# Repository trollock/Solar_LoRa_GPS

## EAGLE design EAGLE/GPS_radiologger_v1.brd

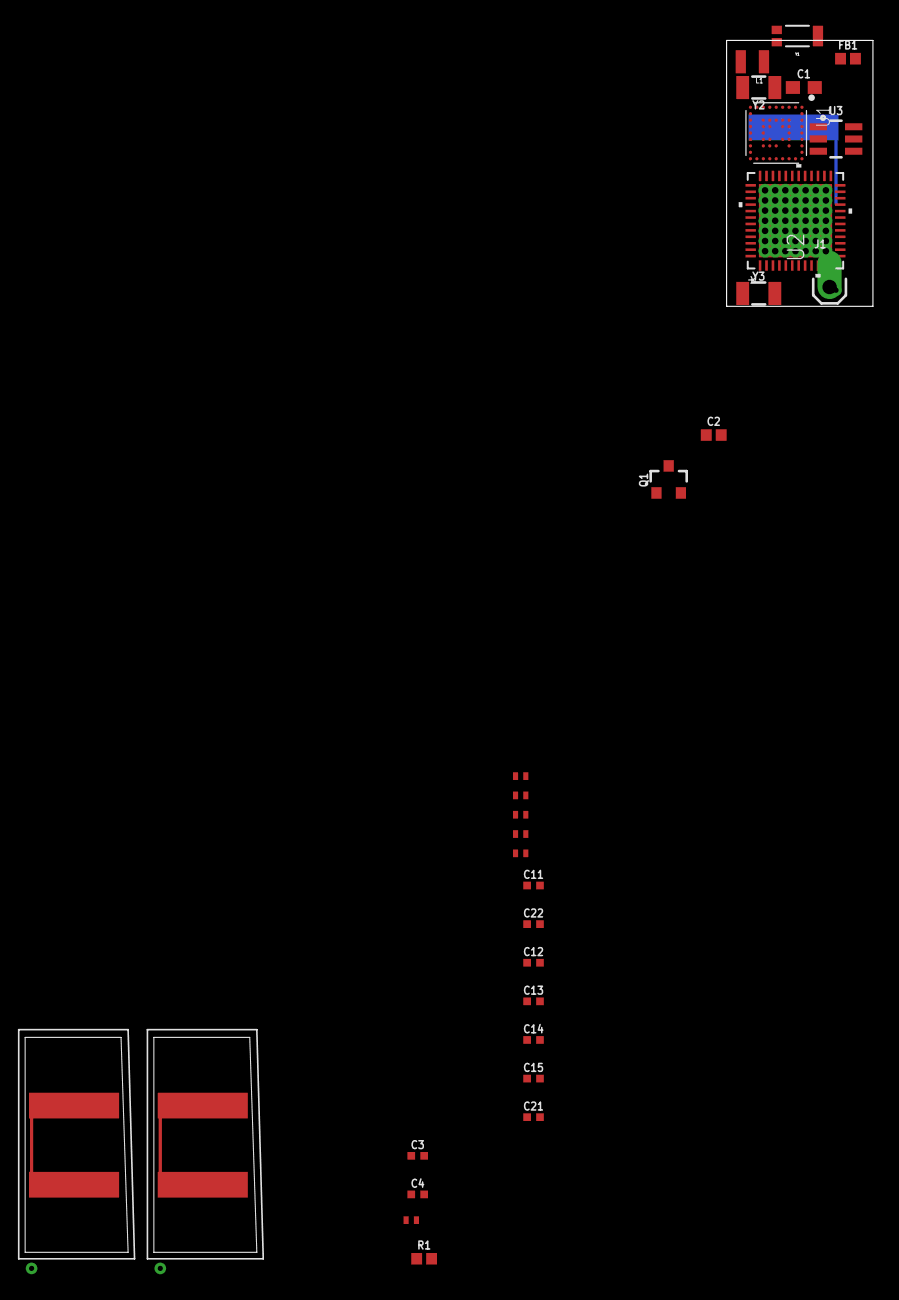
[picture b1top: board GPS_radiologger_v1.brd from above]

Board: 2 copper layers, 11.4 x 20.7 mm, 31 parts (1 on the bottom side), 21 nets, no tracks yet.

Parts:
C1: 4.7pF; 0603
C2: 0.1uF; 0402
C3, C4, C13: 12 pF; 0402-TIGHT
C11, C22: 8.2 pF; 0402-TIGHT
C12, C14: 4.7 pF; 0402-TIGHT
C15, C21: 330 pF; 0402-TIGHT
FB1: 120 Ohm; 0402
J1: 1X01_OFFSET
L1: 2.2 uH; 0806
L11: 33 nH; 0402_MURATA
L12, L21: 15 nH; 0402_MURATA
L13, L14: 20 nH; 0402_MURATA
Q1: 1.1A/60V/600mΩ; SOT23-3
R1: 100K; 0402
U1: UBLOX_ZOE_M8Q-0-10; UBLOX_ZOE_M8-0-10
U2: CC1350F128RGZT; RGZ48
U3: TPL5110; SOT23-6
U$1, U$2, U$4: TRISOLX_8X16
U$3: 2.4 pF; 0402_MURATA
Y1: GPS_CHIP_ANTENNAW3011; W3011
Y2, Y3: 32.768kHz; CRYSTAL-SMD-3.2X1.5MM

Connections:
3.3V: C2.1, U1.24, U1.25
DONE: U2.11, U3.4
DRIVE: Q1.1, U3.5
GND: C1.2, C2.2, C3.2, C4.2, C11.2, C12.2, C13.2, C14.2, C21.2, U1.1, U1.3, U1.5, U1.7, U1.8, U1.9, U1.10, U1.11, U1.12, U1.17, U1.23, U1.29, U1.31, U1.37, U1.38, U1.39, U1.40, U1.41, U1.44, U1.46, U1.47, U1.49, U3.2, U$3.P$2
unnamed: C1.1, L1.1, U1.27
unnamed: L1.2, U1.26
unnamed: U1.18, Y2.P$2
unnamed: U1.19, Y2.P$1
unnamed: U3.1, U3.6
unnamed: C13.1, L13.P$2, L14.P$1
unnamed: C14.1, C15.1, L14.P$2
unnamed: C12.1, C22.1, L12.P$2, L13.P$1
unnamed: C15.2, J1.1
unnamed: C3.1, U2.4, Y3.P$1
unnamed: C4.1, U2.5, Y3.P$2
unnamed: R1.1, U2.35, U$3.P$1
RF_N: C22.2, L11.P$2, L21.P$2, U2.2
RF_P: C11.1, L11.P$1, L12.P$1, U2.1
RX_TX: C21.1, L21.P$1, U2.3
SCL: U1.32, U2.9
SDA: U1.2, U2.10

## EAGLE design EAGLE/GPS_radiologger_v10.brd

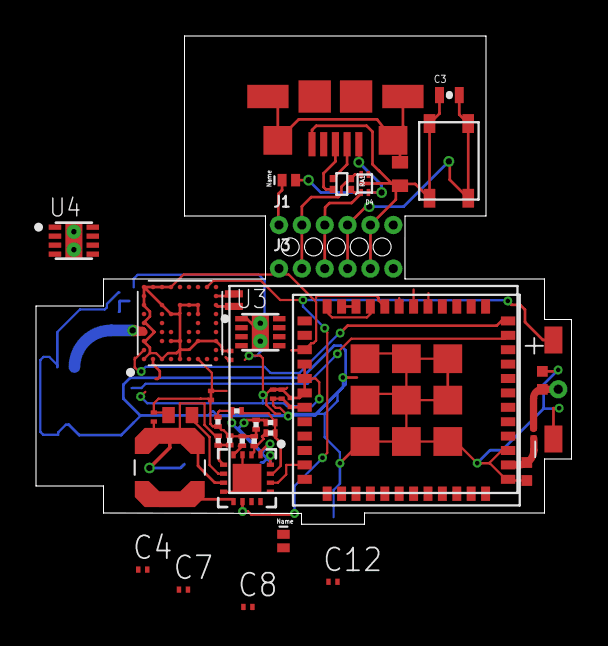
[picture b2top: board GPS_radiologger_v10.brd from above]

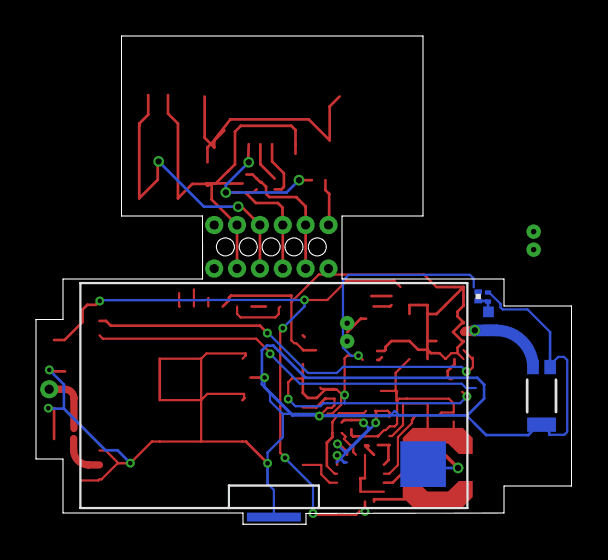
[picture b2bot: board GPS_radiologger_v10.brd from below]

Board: 2 copper layers, 29.8 x 27.1 mm, 47 parts (5 on the bottom side), 40 nets.

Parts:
C1: 47 pF; C0201
C2, C7, C12: 10 uF; C0201
C3: 100 nF; 0402-CAP
C4, C5, C8: 4.7 uF; C0201
C6, C10, C11: 0.1 uF; C0201
C9: 1 uF; C0201
C14: 4.7uF; C0201
C15: 10uF; C0402
D1, D2: CDSQR4148-HF
D4: USBULC6-2N4
FB1: FERRITE_BEAD-120_OHM_TIGHT; 0402-TIGHT
J1, J3: 1X06_1.27MM
J2: 1X01_SMALL
J4: 1981584-1
L1: BLM15HB121SN1; 0402
L3, L4: FERRITE_BEAD-120_OHM_TIGHT; 0402-TIGHT
L5: 22 uH; IND_LPS4012-103MRB
R1: 10; R0201
R2: 6.34M; R0201
R3: 14.7M; R0201
R4: 20k; R0201
RA1: EXB24V
RPG1: 6.8M; R0201
RPG2: 3.3M; R0201
RSD1: 6.49M; R0201
RSD2: 3.48M; R0201
RTERM1: 4.32M; R0201
RTERM2: 5.62M; R0201
U1: TYPEABZ
U2: UBLOX_ZOE_M8-0-10
U3, U4: MICROCHIP_MCP1810T-33I-J8AMICROCHIP_MCP1810T-33I-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; MICROCHIP_MCP1810T-33I-J8A_0
U$1: GMB301016
U$3: ADP5090; LFCSP-16-3X3
U$4: ICARUS_FULL
U$6: C&KTACTILESWITCH
Y1: 32.768kHz; CRYSTAL-SMD-1.0X1.2MM
Y2: W3011

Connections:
ANT: C11.1, J2.P$1, L4.1
BAT: U2.16, U$1.+, U$3.10
BOOT: J3.6, U1.P$43
DCDC_OUT: D2.P$2, U$3.11
DIS_SW: U1.P$11, U$3.14
DM: J3.2, U1.P$2
DM1: D4.P$4, J1.2, RA1.P$1
DP: J3.3, U1.P$1
DP1: D4.P$1, J1.3, RA1.P$2
GND: C1.2, C2.1, C3.1, C4.2, C5.2, C6.2, C7.2, C8.2, C9.1, C10.1, C12.2, C14.2, C15.2, D4.P$5, J1.5, J3.5, J4.5, L1.2, L3.2, L4.2, R3.1, R4.1, RPG2.1, RSD2.1, RTERM2.1, U1.P$3, U1.P$7, U1.P$25, U1.P$27, U1.P$44, U1.P$49, U1.P$50, U1.P$51, U1.P$52, U1.P$53, U1.P$54, U1.P$55, U1.P$56, U1.P$57, U2.1, U2.3, U2.5, U2.7, U2.8, U2.9, U2.10, U2.11, U2.12, U2.17, U2.23, U2.29, U2.31, U2.37, U2.38, U2.39, U2.40, U2.41, U2.44, U2.46, U2.47, U2.49, U3.1, U3.9, U4.1, U4.9, U$1.-, U$4.P$2, U$6.P$3, U$6.P$4, Y2.2, Y2.3
GPS_ANT: FB1.1, U2.4, Y2.1
GPS_PWR: C5.1, C6.1, C7.1, R1.2, U2.24, U2.25, U2.27, U4.2, U4.6
MCU_PWR: C2.2, C9.2, C10.2, C12.1, U1.P$4, U1.P$5, U1.P$6, U3.2, U3.6
unnamed: U1.P$45, U1.P$48
unnamed: D1.P$1, J1.1
unnamed: L5.2, U$3.9
unnamed: U$3.3, U$3.8, U$3.EXP
unnamed: R2.1, R3.2, U$3.5
unnamed: C15.1, U$3.6
unnamed: C1.1, FB1.2, R1.1
unnamed: R4.2, U$3.4
unnamed: RTERM1.1, RTERM2.2, U$3.2
unnamed: RPG1.1, RPG2.2, U$3.16
unnamed: U2.18, Y1.P$2
unnamed: U2.19, Y1.P$1
unnamed: RSD1.1, RSD2.2, U$3.1
unnamed: RPG1.2, RSD1.2, RTERM1.2, U$3.15
unnamed: C4.1, U4.7
unnamed: J4.3, RA1.P$4
unnamed: C11.2, L3.1, U1.P$26
unnamed: J4.2, RA1.P$3
RESET: C3.2, J1.4, U$6.P$1, U$6.P$2
RST: J3.4, U1.P$34
SCL: U1.P$35, U2.32
SDA: U1.P$36, U2.2
TCXO_OUT: U1.P$46, U1.P$47
USB_SHIELD: J4.S1, J4.S2, J4.S3, J4.S4, L1.1
VBUS: C8.1, D2.P$1, J3.1, U1.P$20, U3.7, U3.8
VBUS1: D1.P$2, D4.P$2, J4.1
VIN: C14.1, L5.1, R2.2, U$3.7, U$4.P$1

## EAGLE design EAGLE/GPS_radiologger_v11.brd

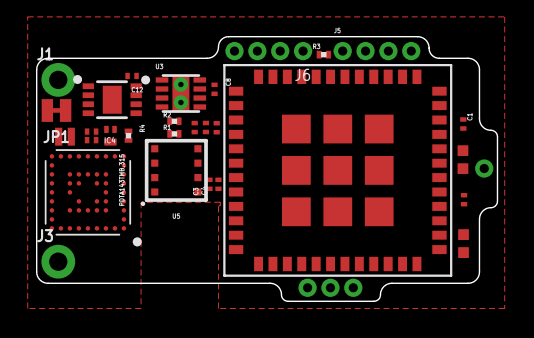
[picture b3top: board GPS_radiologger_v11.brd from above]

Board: 4 copper layers, 25.6 x 14.7 mm, 32 parts (1 on the bottom side), 24 nets, no tracks yet.

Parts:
C1, C3, C4, C6, C10, C11: 0.1 uF; C0201
C2, C12: 10 uF; C0201
C5, C8: 4.7 uF; C0201
C9: 1 uF; C0201
IC4: CAT24M01HU5I-GT3; SON50P300X200X55-9N
J1, J3: 1X01_NO_SILK
J2: 1X01_SMALL
J4: 1X03_1.27MM_NO_SILK
J5, J6: 1X04_1.27MM_NO_SILK
JP1: JUMPER-SMT_2_NC_TRACE_NO-SILK; SMT-JUMPER_2_NC_TRACE_NO-SILK
L3, L4: FERRITE_BEAD-120_OHM_TIGHT; 0402-TIGHT
PDTA143TMB,315: TINYPICO-PNPAMB; SOT883(B)
R1, R2: 4.7; R0201
R3: 10k; R0201
R4: 100k; R0201
U1: TYPEABZ
U2: UBLOX_ZOE_M8-0-10
U3: MICROCHIP_MCP1810T-33I-J8AMICROCHIP_MCP1810T-33I-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; MICROCHIP_MCP1810T-33I-J8A_0
U5: BME680BME680; LGA3.0X3.0
Y1: 32.768kHz; CRYSTAL-SMD-1.0X1.2MM
Y2: W3011

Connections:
ANT: C11.1, J2.P$1, L4.1
BAT: C8.1, J1.1, U1.P$32, U3.7, U3.8
BOOT: J5.1, R3.2, U1.P$43
DM: J6.2, U1.P$2
DP: J6.3, U1.P$1
GND: C1.2, C2.1, C3.2, C4.2, C5.2, C6.2, C8.2, C9.1, C10.1, C12.2, IC4.4, IC4.9, J3.1, J6.4, L3.2, L4.2, R3.1, U1.P$3, U1.P$7, U1.P$25, U1.P$27, U1.P$44, U1.P$49, U1.P$50, U1.P$51, U1.P$52, U1.P$53, U1.P$54, U1.P$55, U1.P$56, U1.P$57, U2.1, U2.3, U2.5, U2.7, U2.8, U2.9, U2.10, U2.11, U2.12, U2.17, U2.23, U2.29, U2.31, U2.37, U2.38, U2.39, U2.40, U2.41, U2.44, U2.46, U2.47, U2.49, U3.1, U3.9, U5.1, U5.7, Y2.2, Y2.3
GPS_ANT: U2.4, Y2.1
unnamed: U1.P$45, U1.P$48
unnamed: JP1.2, U2.16
unnamed: U2.18, Y1.P$2
unnamed: U2.19, Y1.P$1
unnamed: C11.2, L3.1, U1.P$26
POWER: C2.2, C3.1, C4.1, C9.2, C10.2, C12.1, IC4.8, PDTA143TMB,315.2, R1.2, R2.2, R4.2, U1.P$4, U1.P$5, U1.P$6, U3.2, U3.6, U5.6, U5.8
RST: C1.1, J5.4, U1.P$34
RX: J4.2, U1.P$18
SCL: IC4.6, R2.1, U1.P$35, U2.32, U5.4
SDA: IC4.5, R1.1, U1.P$36, U2.2, U5.3
SWDCLK: J5.2, U1.P$42
SWDIO: J5.3, U1.P$41
TCXO_OUT: U1.P$46, U1.P$47
TX: J4.3, U1.P$19
VBUS: J6.1, U1.P$20
ZOE_PDTA: PDTA143TMB,315.1, R4.1, U1.P$24
ZOE_PWR: C5.1, C6.1, JP1.1, PDTA143TMB,315.3, U2.24, U2.25, U2.27

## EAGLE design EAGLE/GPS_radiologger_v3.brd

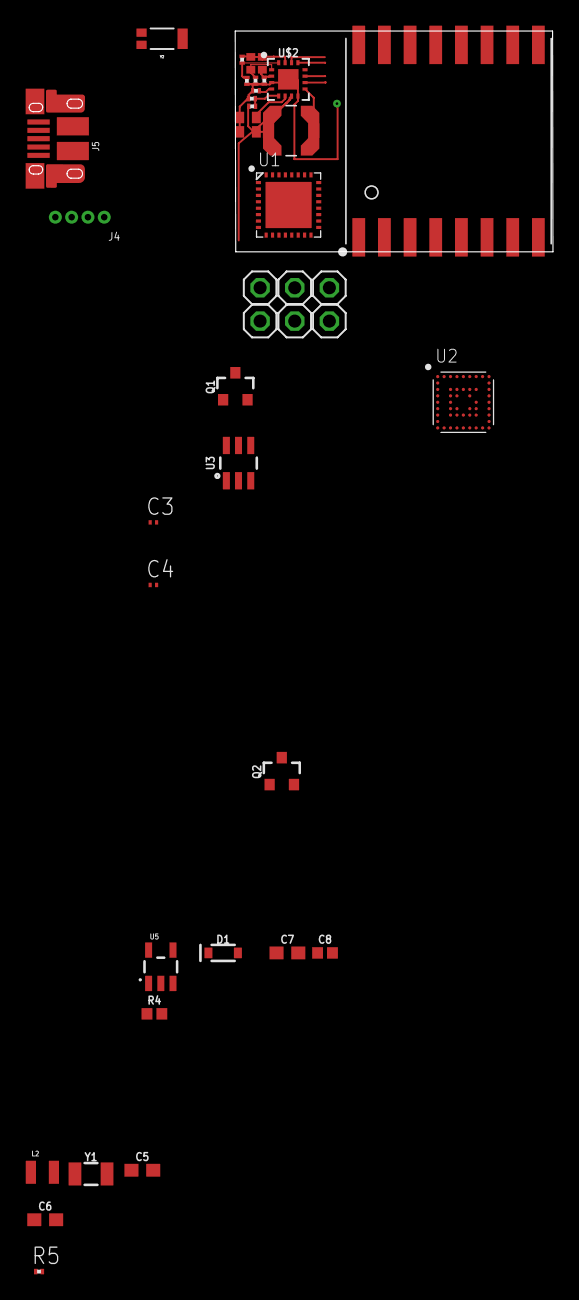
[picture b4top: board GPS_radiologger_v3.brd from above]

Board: 2 copper layers, 40 parts (0 on the bottom side), 37 nets.

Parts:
C1: 4.7uF; C0402
C2: 10uF; C0402
C3, C4: 10 uF; C0201
C5: 4.7uF; 0603
C6: 0.1uF; 0603
C7: 10uF; 0603
C8: 1.0uF; 0402
D1: 1A/23V/620mV; SOD-323
J4: 1X04_1.27MM_NO_SILK
J5: USB-MICROB-PTH-MILL
JP1, JP2, JP3, JP4, JP5, JP6: 1X01
L1: 22 uH; IND_LPS4012-103MRB
L2: 2.2uH; 0806
Q1: 1.1A/60V/600mΩ; SOT23-3
Q2: 3.1A/30V/105mΩ; SOT23-3
R1: 6.34M; R0201
R2: 14.7M; R0201
R3: 20k; R0201
R4: 10k; 0402
R5: 10k; R0201
RPG1, RPG2: R0201
RSD1: R0402
RSD2: R0201
RTERM1: R0402
RTERM2: R0201
U1: ATSAMD21E18A-U; QFN-32_SAMD
U2: UBLOX_ZOE_M8-0-10
U3: TPL5110; SOT23-6
U4: RFM95W; RFM95/96/97/98W
U5: 3.3V; SOT23-5
U$2: ADP5090; LFCSP-16-3X3
Y1: 32.768kHz; CRYSTAL-SMD-3.2X1.5MM
Y2: W3011

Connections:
3.3V: C3.1, C6.1, C7.1, C8.1, R5.2, U1.VDD, U1.VDDIN, U2.24, U2.25, U4.3.3V, U5.5
!RESET: J4.1, U2.20
BAT: JP4.1, U$2.10
D+: J5.D+, U1.PA25
D-: J5.D-, U1.PA24
DIS_SW: JP3.1, U$2.14
DRIVE: Q1.1, U3.5
GND: C1.2, C2.2, C3.2, C4.2, C5.2, C6.2, C7.2, C8.2, J4.2, J5.GND, J5.SHIELD, J5.SHIELD2, J5.SHIELD3, J5.SHIELD4, J5.SHIELD5, J5.SHIELD6, J5.SHIELD7, J5.SHIELD8, J5.SHIELD9, J5.SHIELD10, JP5.1, R2.1, R3.1, R4.1, RPG2.1, RSD2.1, RTERM2.1, U1.GND, U1.GNDANA, U1.PAD, U2.1, U2.3, U2.5, U2.7, U2.8, U2.9, U2.10, U2.11, U2.12, U2.17, U2.23, U2.29, U2.31, U2.37, U2.38, U2.39, U2.40, U2.41, U2.44, U2.46, U2.47, U2.49, U3.2, U4.GND@1, U4.GND@2, U4.GND@3, U5.2, U$2.3, U$2.8, U$2.EXP
MISO: U1.PA05, U4.MISO
MOSI: U1.PA06, U4.MOSI
unnamed: R1.1, R2.2, U$2.5
unnamed: C2.1, U$2.6
unnamed: L1.2, U$2.9
unnamed: L2.2, U2.26
unnamed: R3.2, U$2.4
unnamed: U3.1, U3.6
unnamed: RTERM1.1, RTERM2.2, U$2.2
unnamed: RPG1.1, RPG2.2, U$2.16
unnamed: RSD1.1, RSD2.2, U$2.1
unnamed: C4.1, U1.VDDCORE
unnamed: RPG1.2, RSD1.2, RTERM1.2, U$2.15
unnamed: C5.1, L2.1, U2.27
unnamed: U2.18, Y1.P$2
unnamed: U2.19, Y1.P$1
PGOOD: JP1.1, U$2.13
RFM_CS: R5.1, U1.PA00, U4.NSS
RFM_INT: U1.PA01, U4.DIO0
RFM_RST: U1.PA22, U4.!RESET
SCK: U1.PA07, U4.SCK
SCL: U1.PA09, U2.32
SDA: U1.PA08, U2.2
SWCLK: J4.3, U1.PA30
SWDIO: J4.4, U1.PA31
SYS: JP2.1, U$2.11
VIN: C1.1, D1.C, JP6.1, L1.1, Q2.2, R1.2, U5.1, U5.3, U$2.7
V_BATT: Q2.3, U2.16
V_USB: D1.A, J5.VBUS, Q2.1, R4.2

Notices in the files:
parts and their libraries:
SparkFun-Coils: Licensing: Creative Commons ShareAlike 4.0 International - https://creativecommons.org/licenses/by-sa/4.0
con-usb: Copyright (C) 2008, Bob Starr
